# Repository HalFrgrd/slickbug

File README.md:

# SlickBug

A small SWD programmer using the Seeed Studio XIAO RP2040.
I wanted a compact debugger with a tiny target footprint (roughly 4.8mm by 1.1mm).

It uses four R50 test probe receptacles which are mounted on the back of the PCB and are held in place using two PCB "combs".
P50 test probes sit in the R50 receptacles.  The GND pin extends 1.5mm further so that GND connects first.

## Target footprint

The target footprint is 4 pads with pitch 1.27mm:

|  |   |  |
| :---: | :---: | :---: |
| PCB footprint with guiding hole | PCB footprint SMD only | Target footprint next to a MX keyswitch |

### Installing the target footprint

A standalone KiCad library containing only the target symbol and footprint is located in [`hardware/slick_bug_target/`](hardware/slick_bug_target/)

Add it to your KiCad project with:
1. Copy [`hardware/slick_bug_target/`](hardware/slick_bug_target/) into your project (or add this repo as a submodule).
2. Register the `Footprint Library`: Go to `Preferences->Manage Footprint Libraries`, click the folder icon, and select [`hardware/slick_bug_target/slick_bug_target.pretty`](hardware/slick_bug_target/slick_bug_target.pretty)
3. Register the `Symbol Library`: Go to `Preferences->Manage Symbol Libraries`, add [`hardware/slick_bug_target/slick_bug_target.kicad_sym`](hardware/slick_bug_target/slick_bug_target.kicad_sym)
4. Place `slick_bug_target:Conn_SWD_SlickBug_V1` in your schematic. It already has `slick_bug_target:SlickBug_Target_V1` pre-assigned as its footprint.

### Ordering and assembly

Drag the [production files](hardware/production/slick_bug.zip) to JLCPCB's order page to get the PCBs. 1.6mm thick so that the combs work as intended.

You can get the [components](hardware/production/bom.csv) from LCSC and combine your order with JLCPCB. I bought the test probes and receptacles from AliExpress.

You will need to snap off the combs from the pcb to hold the R50 receptacles in place.

|  |  |
| :---: | :---: |
| SlickBug PCB | Partly assembled |

### Firmware

SlickBug uses the same SWD GPIO pins (`GPIO 2` = SWCLK, `GPIO 3` = SWDIO) as a Raspberry Pi Pico, so it runs the unmodified official [**`debugprobe_on_pico.uf2`**](https://github.com/raspberrypi/debugprobe/releases/latest) firmware (also included in [`firmware/debugprobe_on_pico.uf2`](firmware/debugprobe_on_pico.uf2)):

1. Put the XIAO RP2040 into BOOTSEL mode (hold **`B`**, tap **`R`**, release **`B`**).
2. Copy [`firmware/debugprobe_on_pico.uf2`](firmware/debugprobe_on_pico.uf2) onto the `RPI-RP2` drive.

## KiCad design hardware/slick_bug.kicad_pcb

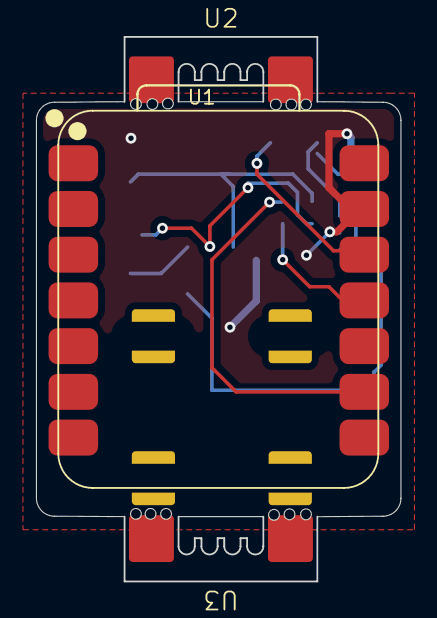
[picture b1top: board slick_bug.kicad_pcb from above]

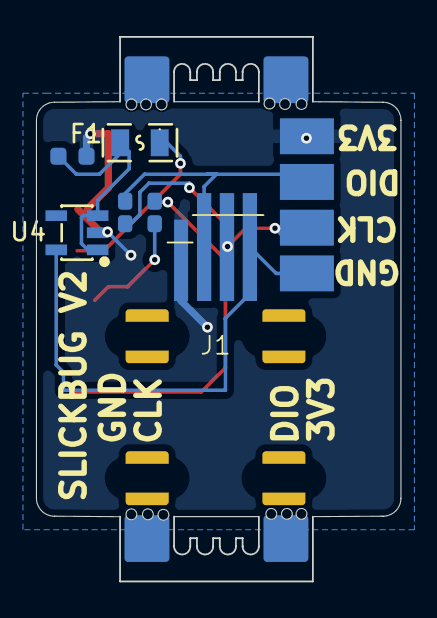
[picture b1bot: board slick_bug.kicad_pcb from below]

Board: 2 copper layers, 20.2 x 30.3 mm, 10 parts (7 on the bottom side), 8 nets.

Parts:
C1: 1uF; C_0603
F1: JK-SMD0805-020-30V; F0805
J1: Conn_01x04_Socket; R50_horizontal_4pin
J2: Conn_01x04_Socket; Harwin_M20-89004xx_1x04_P2.54mm_Horizontal_blank
R1, R2: 33Ω; R_0603
U1: XIAO-RP2040-SMD
U2, U3: R50_pcb_comb
U4: MAX40203AUK+T; SOT-23-5_L3.0-W1.6-P0.95-LS2.8-BR

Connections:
GND: C1.2, J1.1, J2.1, U1.13 (GND), U4.2 (GND)
unnamed: F1.1, U1.12 (3V3_OUT)
unnamed: R2.1, U1.9 (D8)
unnamed: R1.1, U1.11 (D10)
unnamed: C1.1, F1.2, U4.1 (VDD), U4.3 (EN)
TARGET_SWCLK: J1.2, J2.2, R2.2
TARGET_SWDIO: J1.3, J2.3, R1.2
TARGET_VCC: J1.4, J2.4, U4.5 (OUT)

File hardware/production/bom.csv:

Designator,Footprint,Quantity,Value,LCSC Part #
C1,C_0603,1,1uF,C15849
F1,F0805,1,JK-SMD0805-020-30V,C516070
"R1, R2",R_0603,2,33Ω,C23140
U4,SOT-23-5_L3.0-W1.6-P0.95-LS2.8-BR,1,MAX40203AUK+T,C2653639
